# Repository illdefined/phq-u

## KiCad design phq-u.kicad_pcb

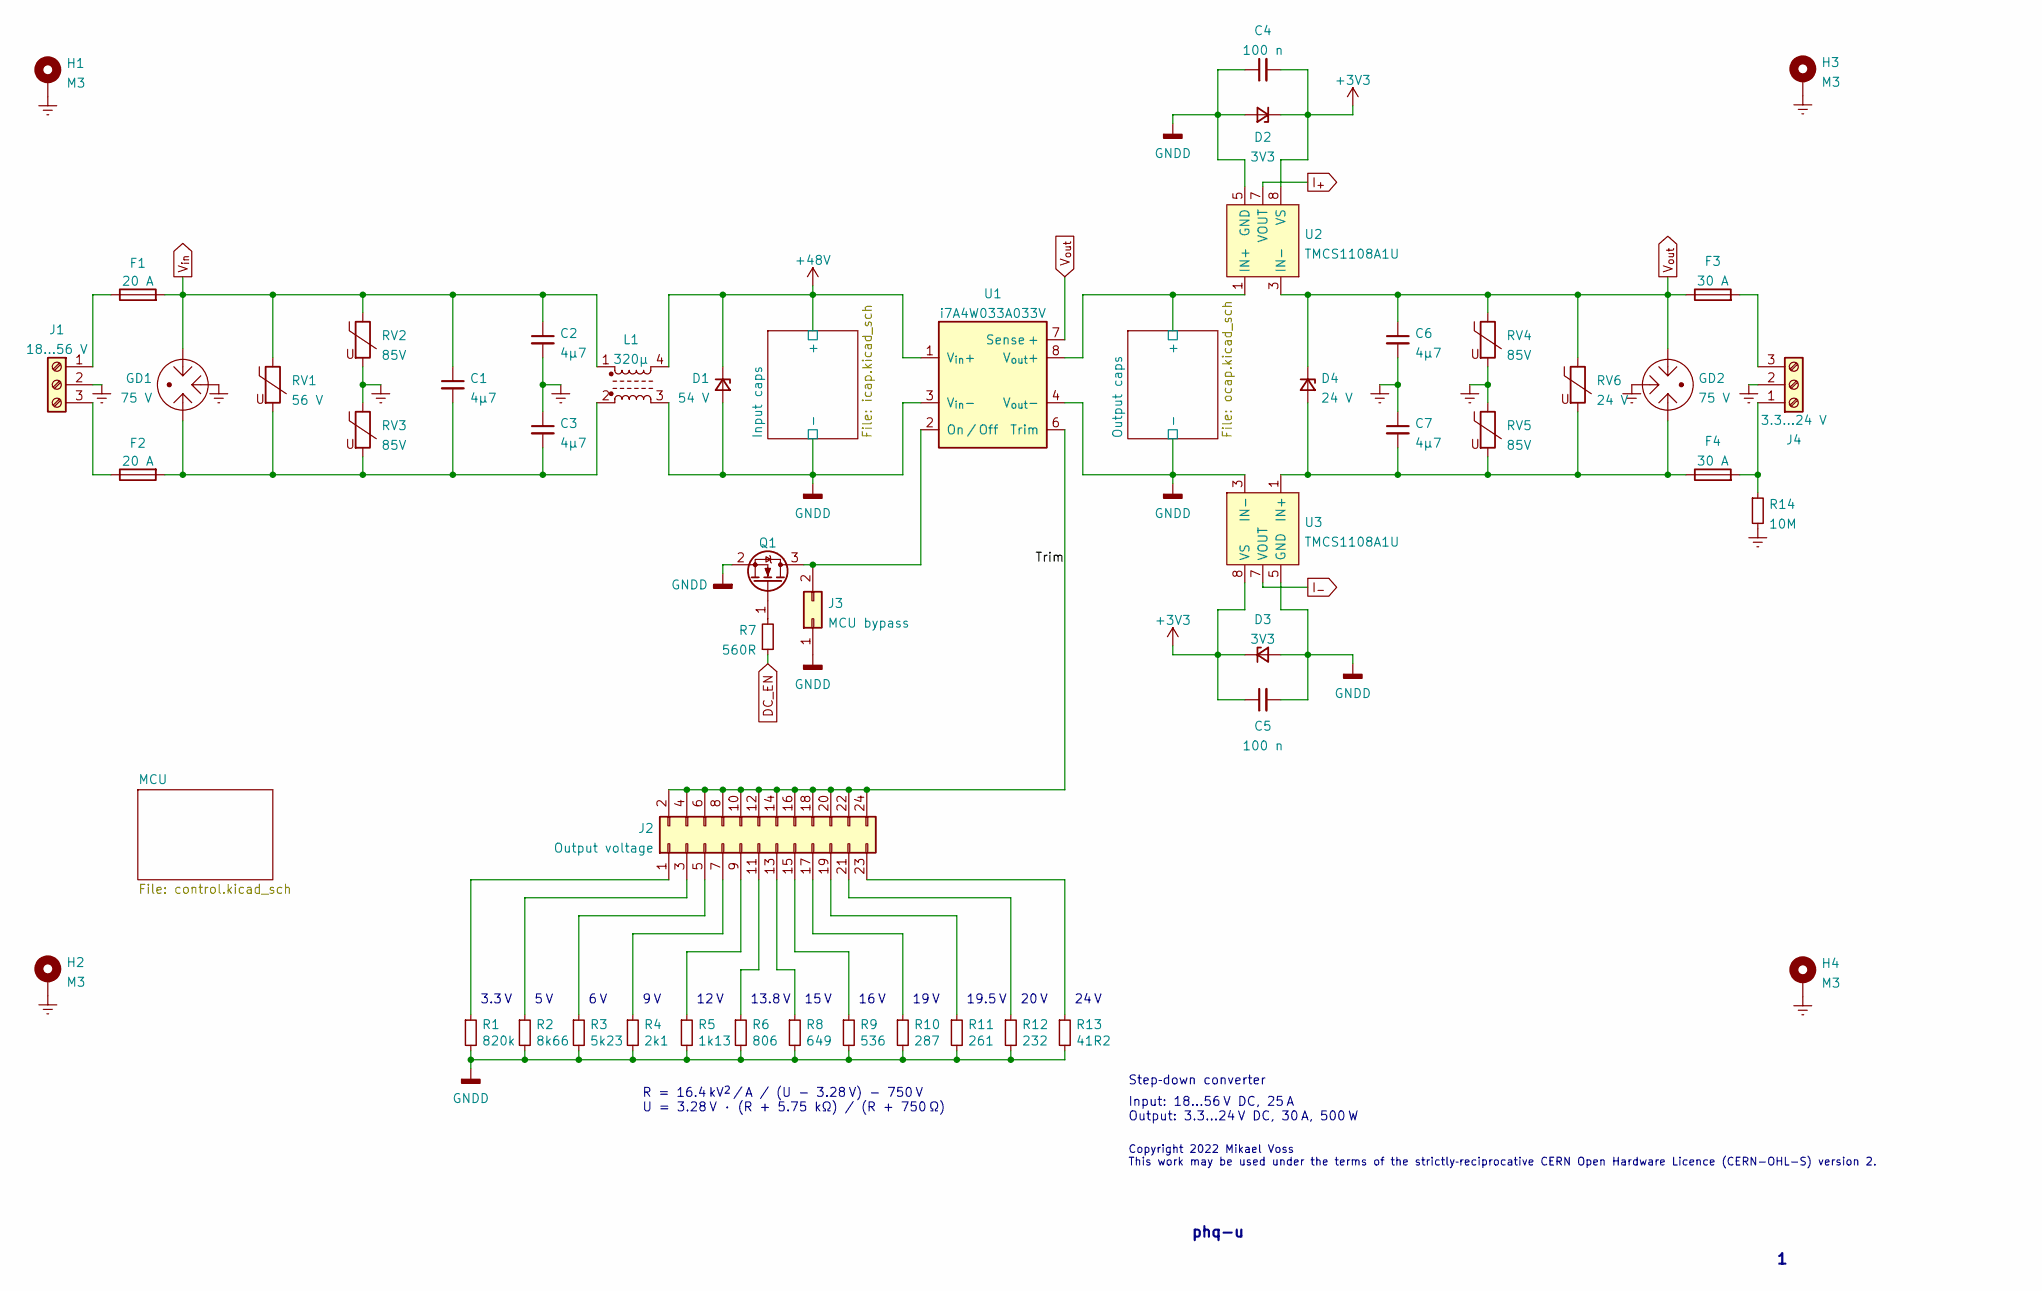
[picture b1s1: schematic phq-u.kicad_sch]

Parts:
C1, C2, C3, C6, C7: 4µ7; C_1210_3225Metric; Part Number 12101C475K4T2A
C4, C5: 100 n; C_0402_1005Metric
D1: 54 V; D_SMB; Part Number 1.5SMBJ54A-H
D2, D3: 3V3; D_0402_1005Metric; Part Number DF2S5M4CT
D4: 24 V; D_SMA; Part Number SMA6F24A
F1, F2: 20 A; Fuse_2410_20A; Part Number CB61F30A
F3, F4: 30 A; Fuse_2410_20A; Part Number CB61F30A
GD1, GD2: 75 V; 2036-NN-SM; Part Number 2036-07-SM
H1, H2, H3, H4: M3; MountingHole_3.2mm_M3_Pad_Via
J1: 18…56 V; Phoenix_1987737
J2: Output voltage; PinHeader_2x12_P2.00mm_Vertical
J3: MCU bypass; PinHeader_2x01_P2.00mm_Vertical
J4: 3.3…24 V; Phoenix_1987737
L1: 320µ; CMX1211Z321B-10
Q1: NX138AKR; SOT-23; Part Number NX138AKR
R1: 820k; R_0603_1608Metric
R2: 8k66; R_0603_1608Metric
R3: 5k23; R_0603_1608Metric
R4: 2k1; R_0603_1608Metric
R5: 1k13; R_0603_1608Metric
R6: 806; R_0603_1608Metric
R7: 560R; R_0402_1005Metric
R8: 649; R_0603_1608Metric
R9: 536; R_0603_1608Metric
R10: 287; R_0603_1608Metric
R11: 261; R_0603_1608Metric
R12: 232; R_0603_1608Metric
R13: 41R2; R_0603_1608Metric
R14: 10M; R_0603_1608Metric
RV1: 56 V; C_2220_5650Metric; Part Number B72540E0400K062
RV2, RV3, RV4, RV5: 85V; C_1206_3216Metric; Part Number ZV60K1206121NIR1
RV6: 24 V; C_1210_3225Metric; Part Number B72530T6170K062
U1: i7A4W033A033V; i7A4W-0C1; Part Number i7A4W033A033V-0C1
U2, U3: TMCS1108A1U; SOIC-8_3.9x4.9mm_P1.27mm

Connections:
+3V3: C4.2, C5.1, D2.1 (K), D3.1 (K), U2.8 (VS), U3.8 (VS); also elsewhere on the board
+48V: D1.1 (K), L1.4, U1.1 (V_{in}+); also elsewhere on the board
/Output caps/+: U1.8 (V_{out}+), U2.1 (IN+), U2.2 (IN+); also elsewhere on the board
/Trim: J2.2, J2.4, J2.6, J2.8, J2.10, J2.12, J2.14, J2.16, J2.18, J2.20, J2.22, J2.24, U1.6 (Trim)
DC_EN: R7.1; also elsewhere on the board
Earth: C2.2, C3.1, C6.2, C7.1, GD1.2, GD2.2, H1.1, H2.1, H3.1, H4.1, J1.2, J4.2, R14.2, RV2.2, RV3.1, RV4.2, RV5.1
GND: C4.1, C5.2, D1.2 (A), D2.2 (A), D3.2 (A), J3.1, L1.3, Q1.2 (S), R1.2, R2.2, R3.2, R4.2, R5.2, R6.2, R8.2, R9.2, R10.2, R11.2, R12.2, R13.2, U1.3 (V_{in}-), U1.4 (V_{out}-), U2.5 (GND), U2.6 (NC), U3.3 (IN-), U3.4 (IN-), U3.5 (GND), U3.6 (NC); also elsewhere on the board
I_{+}: U2.7 (VOUT); also elsewhere on the board
I_{-}: U3.7 (VOUT); also elsewhere on the board
unnamed: C1.2, C3.2, F2.2, GD1.3, L1.2, RV1.2, RV3.2
unnamed: C7.2, D4.2 (A), F4.1, GD2.1, RV5.2, RV6.2, U3.1 (IN+), U3.2 (IN+)
unnamed: F1.1, J1.1
unnamed: F2.1, J1.3
unnamed: F3.2, J4.3
unnamed: F4.2, J4.1, R14.1
unnamed: J2.1, R1.1
unnamed: J2.3, R2.1
unnamed: J2.5, R3.1
unnamed: J2.7, R4.1
unnamed: J2.9, R5.1
unnamed: J2.11, R6.1
unnamed: J2.13, R8.1
unnamed: J2.15, R9.1
unnamed: J2.17, R10.1
unnamed: J2.19, R11.1
unnamed: J2.21, R12.1
unnamed: J2.23, R13.1
unnamed: J3.2, Q1.3 (D), U1.2 (On / Off)
unnamed: Q1.1 (G), R7.2
V_{in}: C1.1, C2.1, F1.2, GD1.1, L1.1, RV1.1, RV2.1; also elsewhere on the board
V_{out}: C6.1, D4.1 (K), F3.1, GD2.3, RV4.1, RV6.1, U1.7 (Sense +), U2.3 (IN-), U2.4 (IN-); also elsewhere on the board

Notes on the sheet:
12 V
16 V
phq-u
R = 16.4 kV^{2} / A / (U - 3.28 V) - 750 V U = 3.28 V · (R + 5.75 kΩ) / (R + 750 Ω)
15 V
24 V
13.8 V
9 V
Copyright 2022 Mikael Voss This work may be used under the terms of the strictly‐reciprocative CERN Open Hardware Licence (CERN-OHL-S) version 2.
Input: 18…56 V DC, 25 A Output: 3.3…24 V DC, 30 A, 500 W
19.5 V
5 V
19 V
Step‐down converter
6 V
20 V
3.3 V

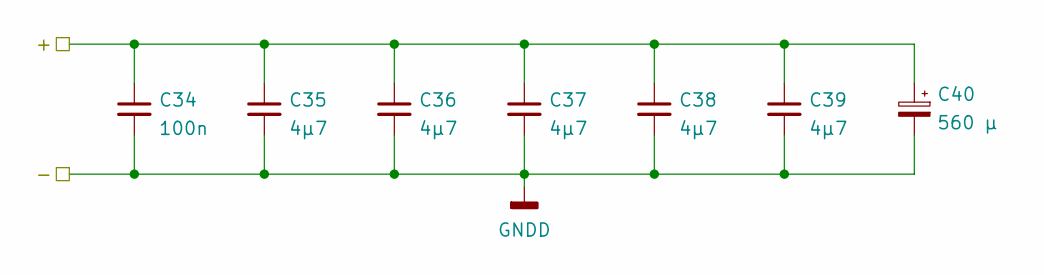
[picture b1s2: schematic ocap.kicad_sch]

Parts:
C34: 100n; C_0402_1005Metric; Part Number GRM155R71H104KE14D
C35, C36, C37, C38, C39: 4µ7; C_1206_3216Metric; Part Number 12065C475KAT2A
C40: 560 µ; CP_Radial_D10.0mm_P5.00mm; Part Number UHV1V561MPD

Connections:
/Output caps/+: C34.1, C35.1, C36.1, C37.1, C38.1, C39.1, C40.1; also elsewhere on the board
GND: C34.2, C35.2, C36.2, C37.2, C38.2, C39.2, C40.2; also elsewhere on the board

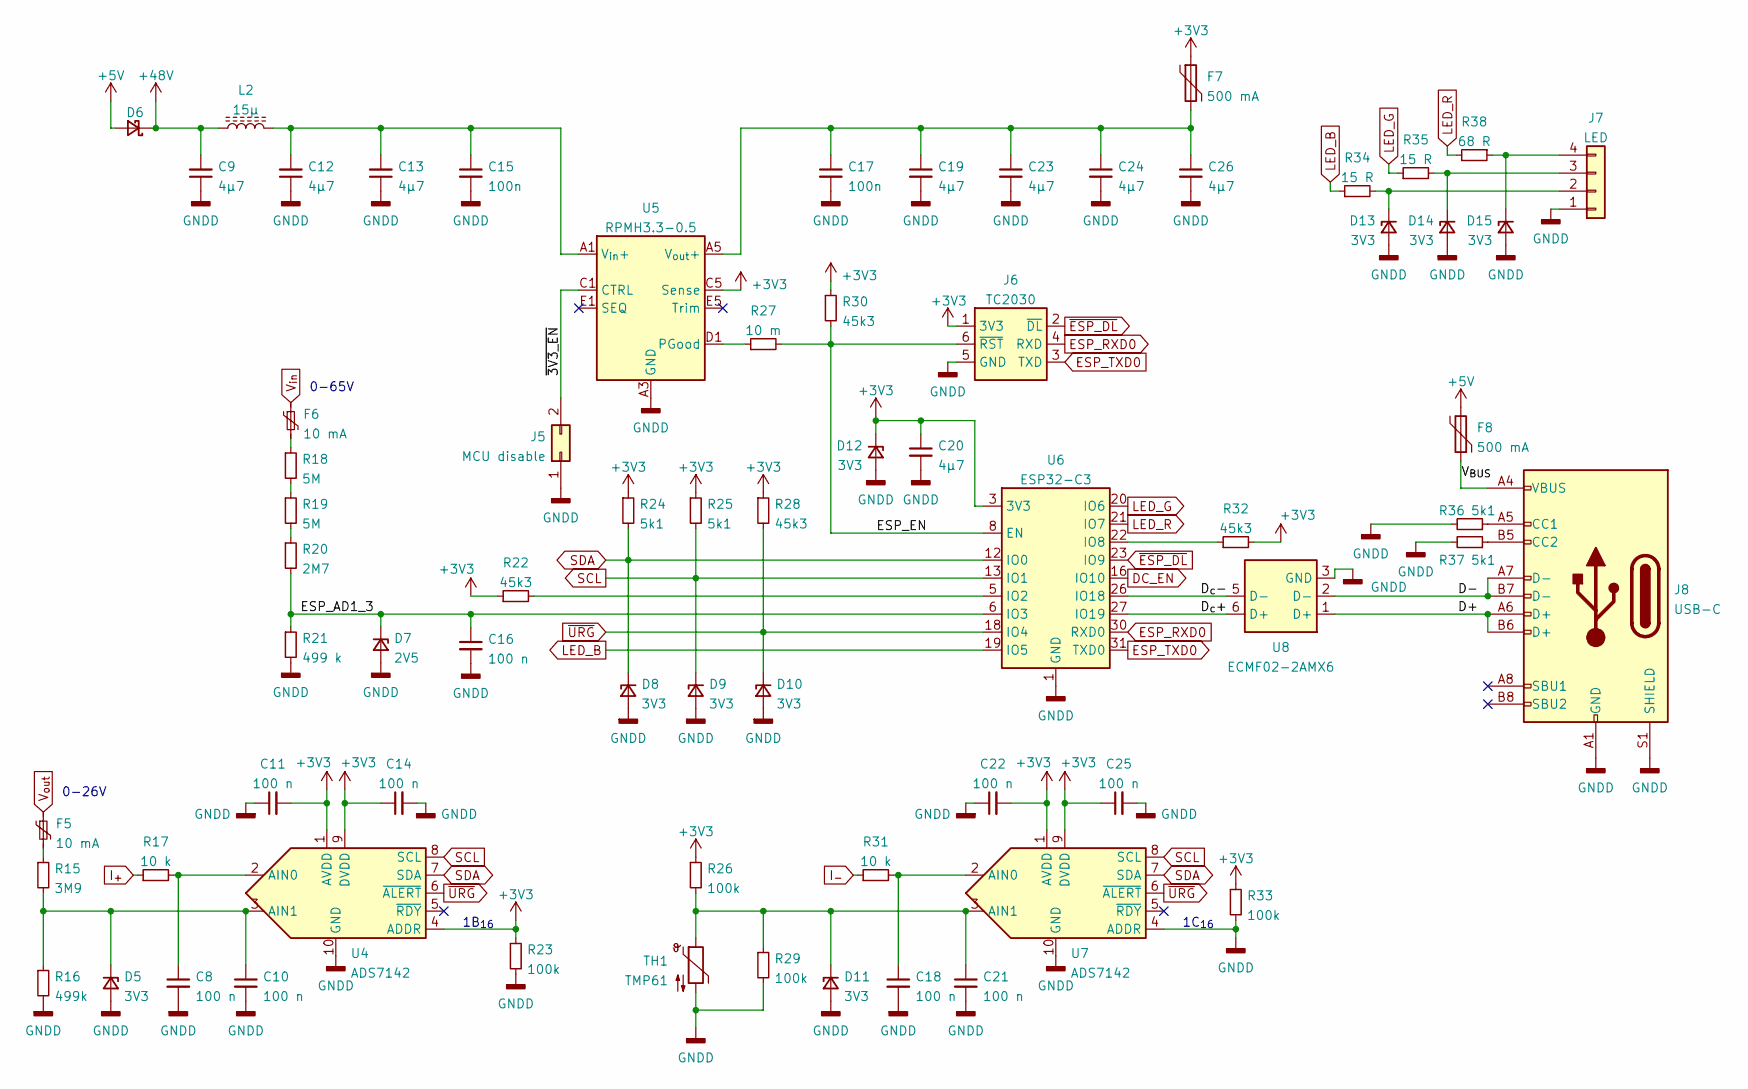
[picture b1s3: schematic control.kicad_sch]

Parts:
C8, C10, C11, C14, C18, C21, C22, C25: 100 n; C_0402_1005Metric; Part Number JMK105B7104KV-F
C9, C12, C13: 4µ7; C_1206_3216Metric; Part Number GRJ31CZ72A475KE01L
C15: 100n; C_0603_1608Metric; Part Number HMK107B7104KA
C16: 100 n; C_0402_1005Metric
C17: 100n; C_0402_1005Metric; Part Number GRM155R71E104KE14J
C19, C20, C23, C24, C26: 4µ7; C_0805_2012Metric; Part Number GRM21BR71A475KE51L
D5, D8, D9, D10, D11, D12, D13, D14, D15: 3V3; D_0402_1005Metric; Part Number DF2S5M4CT
D6: Schottky diode; D_SMF; Part Number SS1FN6
D7: 2V5; D_0402_1005Metric; Part Number UCLAMP2501T.TCT
F5, F6: 10 mA; Fuse_0603_1608Metric; Part Number 0ZCM0001FF2G
F7, F8: 500 mA; Fuse_0603_1608Metric; Part Number MF-FSML050/8-2
J5: MCU disable; PinHeader_2x01_P2.00mm_Vertical
J6: TC2030
J7: LED; PinHeader_1x04_P2.00mm_Vertical
J8: USB-C; USB4120
L2: 15µ; WE-LQS_4018; Part Number 74438356150
R15: 3M9; R_1206_3216Metric
R16: 499k; R_0805_2012Metric
R17, R31: 10 k; R_0402_1005Metric
R18, R19: 5M; R_1206_3216Metric
R20: 2M7; R_1206_3216Metric
R21: 499 k; R_0805_2012Metric
R22, R28, R30, R32: 45k3; R_0402_1005Metric
R23, R26, R29, R33: 100k; R_0402_1005Metric
R24, R25, R36, R37: 5k1; R_0402_1005Metric
R27: 10 m; R_0805_2012Metric
R34, R35: 15 R; R_0402_1005Metric
R38: 68 R; R_0402_1005Metric
TH1: TMP61; R_0402_1005Metric
U4, U7: ADS7142; Texas_R-PUQFN-N10
U5: RPMH3.3-0.5; Converter_DCDC_RECOM_RPMx.x-x.0
U6: ESP32-C3; ESP32-C3-MINI-1U
U8: ECMF02-2AMX6; ST_UQFN-6L_1.5x1.7mm_Pitch0.5mm

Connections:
+3V3: C11.2, C14.1, C20.1, C22.2, C25.1, D12.1 (K), F7.1, J6.1 (3V3), R22.1, R23.1, R24.1, R25.1, R26.1, R28.1, R30.1, R32.2, R33.1, U4.1 (AVDD), U4.4 (ADDR), U4.9 (DVDD), U5.C5 (Sense), U6.3 (3V3), U7.1 (AVDD), U7.9 (DVDD); also elsewhere on the board
+5V: D6.2 (A), F8.2
+48V: C9.2, D6.1 (K), L2.1; also elsewhere on the board
/MCU/D+: J8.A6 (D+), J8.B6 (D+), U8.1 (D+)
/MCU/D-: J8.A7 (D-), J8.B7 (D-), U8.2 (D-)
/MCU/D_{c}+: U6.27 (IO19), U8.6 (D+)
/MCU/D_{c}-: U6.26 (IO18), U8.5 (D-)
/MCU/ESP_AD1_3: C16.1, D7.1 (K), R20.2, R21.1, U6.6 (IO3)
/MCU/ESP_EN: J6.6 (~RST), R27.2, R30.2, U6.8 (EN)
/MCU/V_{BUS}: F8.1, J8.A4 (VBUS), J8.A9 (VBUS), J8.B4 (VBUS), J8.B9 (VBUS)
/MCU/~3V3_EN: J5.2, U5.C1 (CTRL)
DC_EN: U6.16 (IO10); also elsewhere on the board
ESP_RXD0: J6.4 (RXD), U6.30 (RXD0)
ESP_TXD0: J6.3 (TXD), U6.31 (TXD0)
GND: C8.2, C9.1, C10.2, C11.1, C12.1, C13.1, C14.2, C15.2, C16.2, C17.2, C18.2, C19.2, C20.2, C21.2, C22.1, C23.2, C24.2, C25.2, C26.2, D5.2 (A), D7.2 (A), D8.2 (A), D9.2 (A), D10.2 (A), D11.2 (A), D12.2 (A), D13.2 (A), D14.2 (A), D15.2 (A), J5.1, J6.5 (GND), J7.1, J8.A1 (GND), J8.A12 (GND), J8.B1 (GND), J8.B12 (GND), J8.S1 (SHIELD), J8.S2 (SHIELD), J8.S3 (SHIELD), J8.S4 (SHIELD), R16.2, R21.2, R23.2, R29.2, R33.2, R36.2, R37.2, TH1.2, U4.10 (GND), U5.A3 (GND), U5.A4 (GND), U5.B1 (GND), U5.B2 (GND), U5.B3 (GND), U5.B4 (GND), U5.C2 (GND), U5.C3 (GND), U5.C4 (GND), U5.D2 (GND), U5.D3 (GND), U5.D4 (GND), U5.D5 (GND), U5.E3 (GND), U5.E4 (GND), U6.1 (GND), U6.2 (GND), U6.11 (GND), U6.14 (GND), U6.36 (GND), U6.37 (GND), U6.38 (GND), U6.39 (GND), U6.40 (GND), U6.41 (GND), U6.42 (GND), U6.43 (GND), U6.44 (GND), U6.45 (GND), U6.46 (GND), U6.47 (GND), U6.48 (GND), U6.49_1 (GND), U6.49_2 (GND), U6.49_3 (GND), U6.49_4 (GND), U6.49_5 (GND), U6.49_6 (GND), U6.49_7 (GND), U6.49_8 (GND), U6.49_9 (GND), U6.50 (GND), U6.51 (GND), U6.52 (GND), U6.53 (GND), U7.4 (ADDR), U7.10 (GND), U8.3 (GND), U8.4 (NC); also elsewhere on the board
I_{+}: R17.1; also elsewhere on the board
I_{-}: R31.1; also elsewhere on the board
LED_B: R34.1, U6.19 (IO5)
LED_G: R35.1, U6.20 (IO6)
LED_R: R38.2, U6.21 (IO7)
unnamed: C8.1, R17.2, U4.2 (AIN0)
unnamed: C10.1, D5.1 (K), R15.2, R16.1, U4.3 (AIN1)
unnamed: C12.2, C13.2, C15.1, L2.2, U5.A1 (V_{in}+), U5.A2 (V_{in}+)
unnamed: C17.1, C19.1, C23.1, C24.1, C26.1, F7.2, U5.A5 (V_{out}+), U5.B5 (V_{out}+)
unnamed: C18.1, R31.2, U7.2 (AIN0)
unnamed: C21.1, D11.1 (K), R26.2, R29.1, TH1.1, U7.3 (AIN1)
unnamed: D13.1 (K), J7.2, R34.2
unnamed: D14.1 (K), J7.3, R35.2
unnamed: D15.1 (K), J7.4, R38.1
unnamed: F5.2, R15.1
unnamed: F6.2, R18.1
unnamed: J8.A5 (CC1), R36.1
unnamed: J8.B5 (CC2), R37.1
unnamed: R18.2, R19.1
unnamed: R19.2, R20.1
unnamed: R22.2, U6.5 (IO2)
unnamed: R27.1, U5.D1 (PGood)
unnamed: R32.1, U6.22 (IO8)
SCL: D9.1 (K), R25.2, U4.8 (SCL), U6.13 (IO1), U7.8 (SCL)
SDA: D8.1 (K), R24.2, U4.7 (SDA), U6.12 (IO0), U7.7 (SDA)
V_{in}: F6.1; also elsewhere on the board
V_{out}: F5.1; also elsewhere on the board
~ESP_DL: J6.2 (~DL), U6.23 (IO9)
~URG: D10.1 (K), R28.2, U4.6 (~ALERT), U6.18 (IO4), U7.6 (~ALERT)

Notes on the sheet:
1C_{16}
0-26V
0-65V
1B_{16}

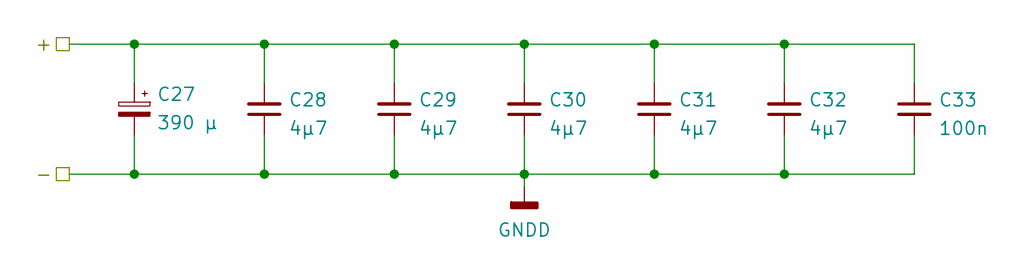
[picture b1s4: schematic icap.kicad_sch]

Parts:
C27: 390 µ; CP_Radial_D12.5mm_P5.00mm; Part Number UHW1J391MHD6
C28, C29, C30, C31, C32: 4µ7; C_1206_3216Metric; Part Number GRJ31CZ72A475KE01L
C33: 100n; C_0603_1608Metric; Part Number HMK107B7104KA

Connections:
+48V: C27.1, C28.2, C29.2, C30.2, C31.2, C32.2, C33.1; also elsewhere on the board
GND: C27.2, C28.1, C29.1, C30.1, C31.1, C32.1, C33.2; also elsewhere on the board

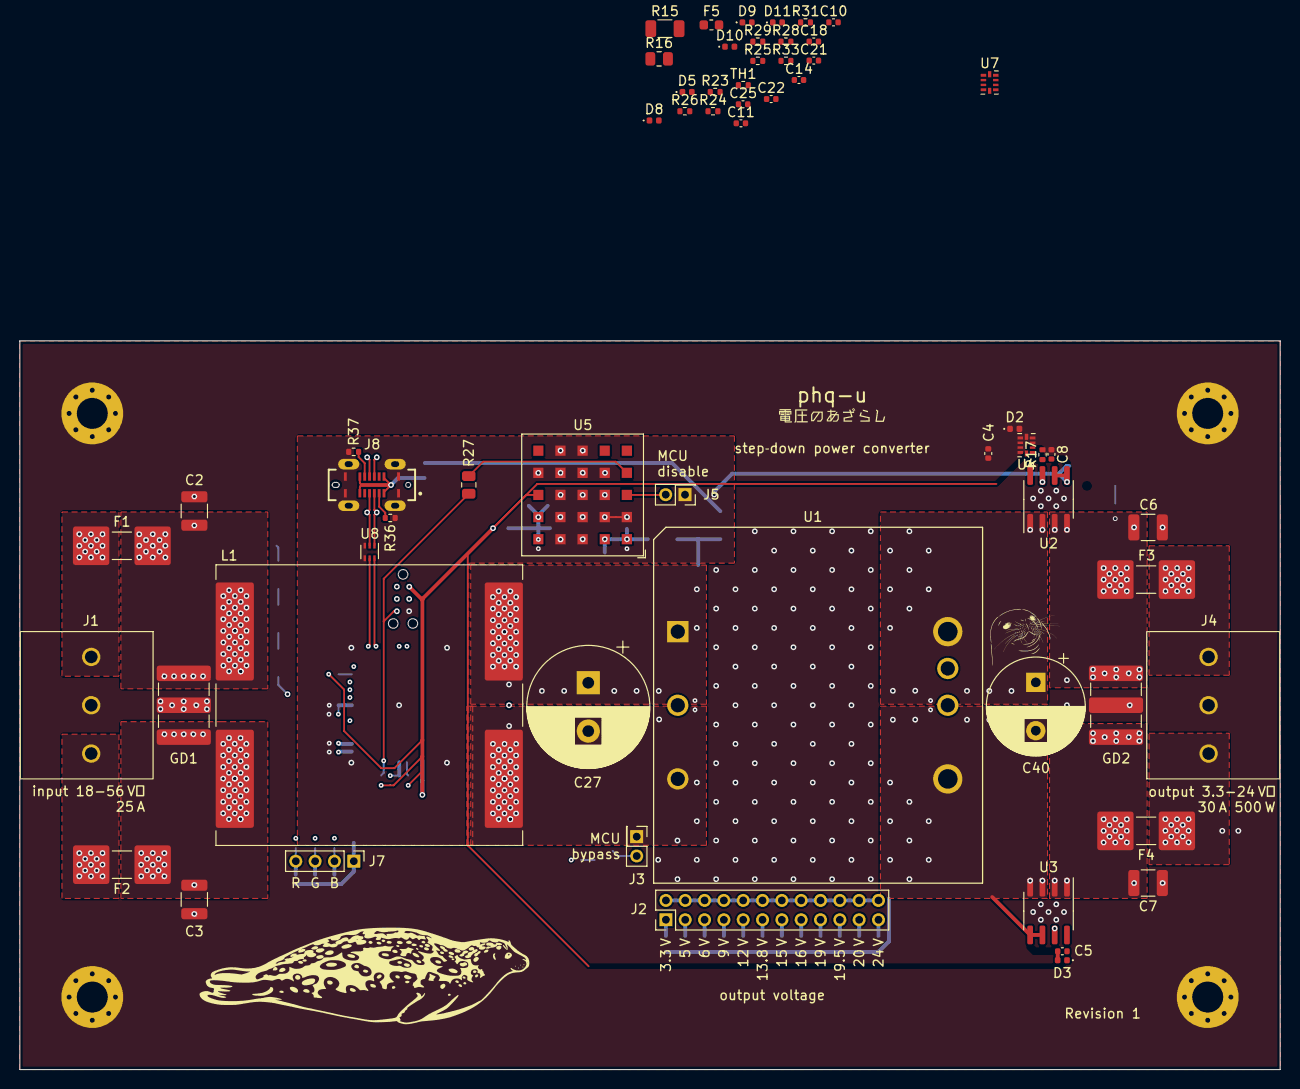
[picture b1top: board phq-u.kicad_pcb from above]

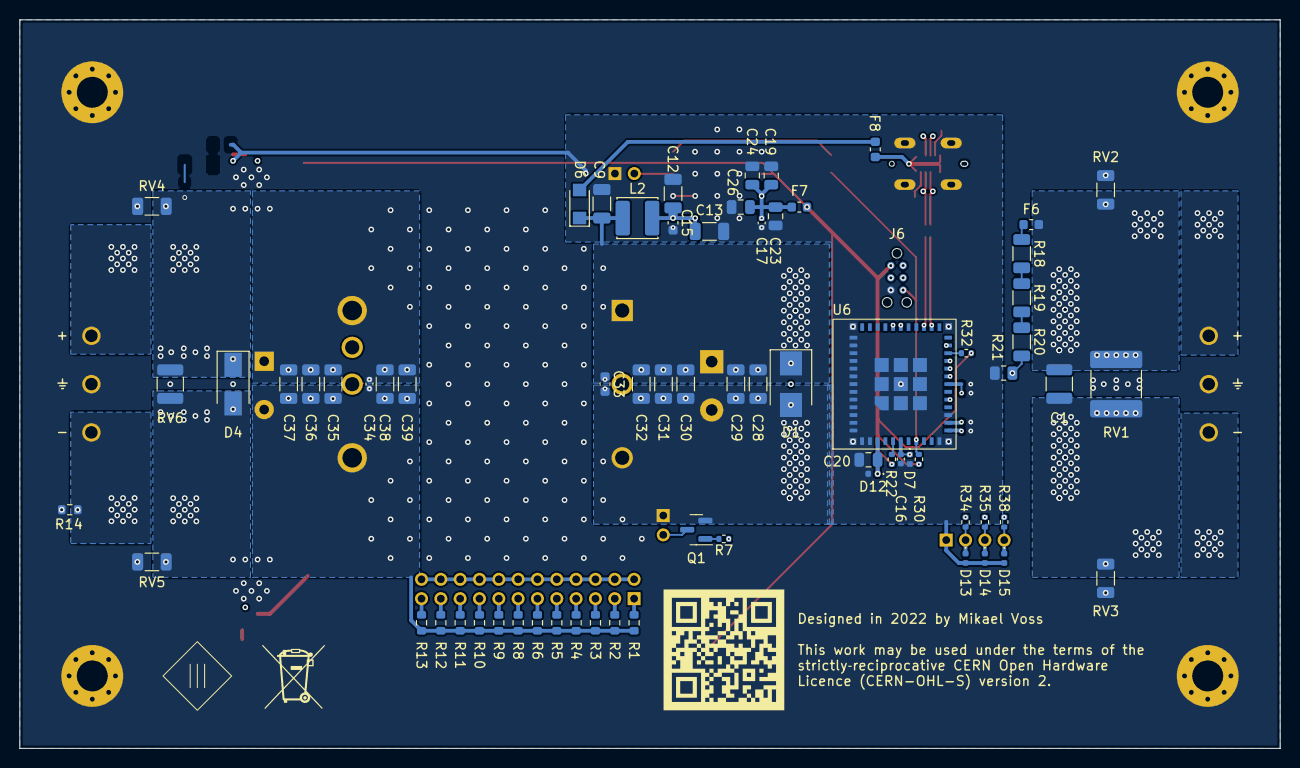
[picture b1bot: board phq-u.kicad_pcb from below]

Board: 4 copper layers, 130.4 x 75.4 mm, 133 parts (69 on the bottom side), 67 nets.

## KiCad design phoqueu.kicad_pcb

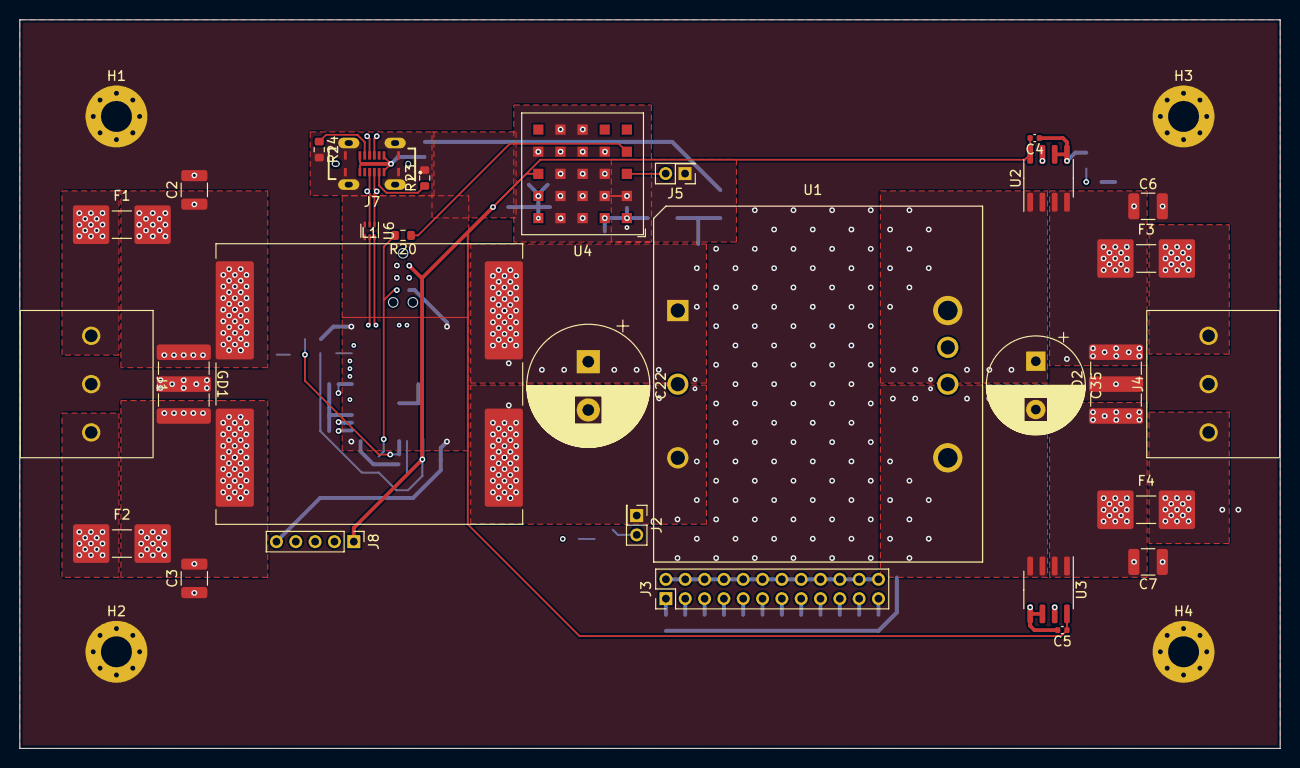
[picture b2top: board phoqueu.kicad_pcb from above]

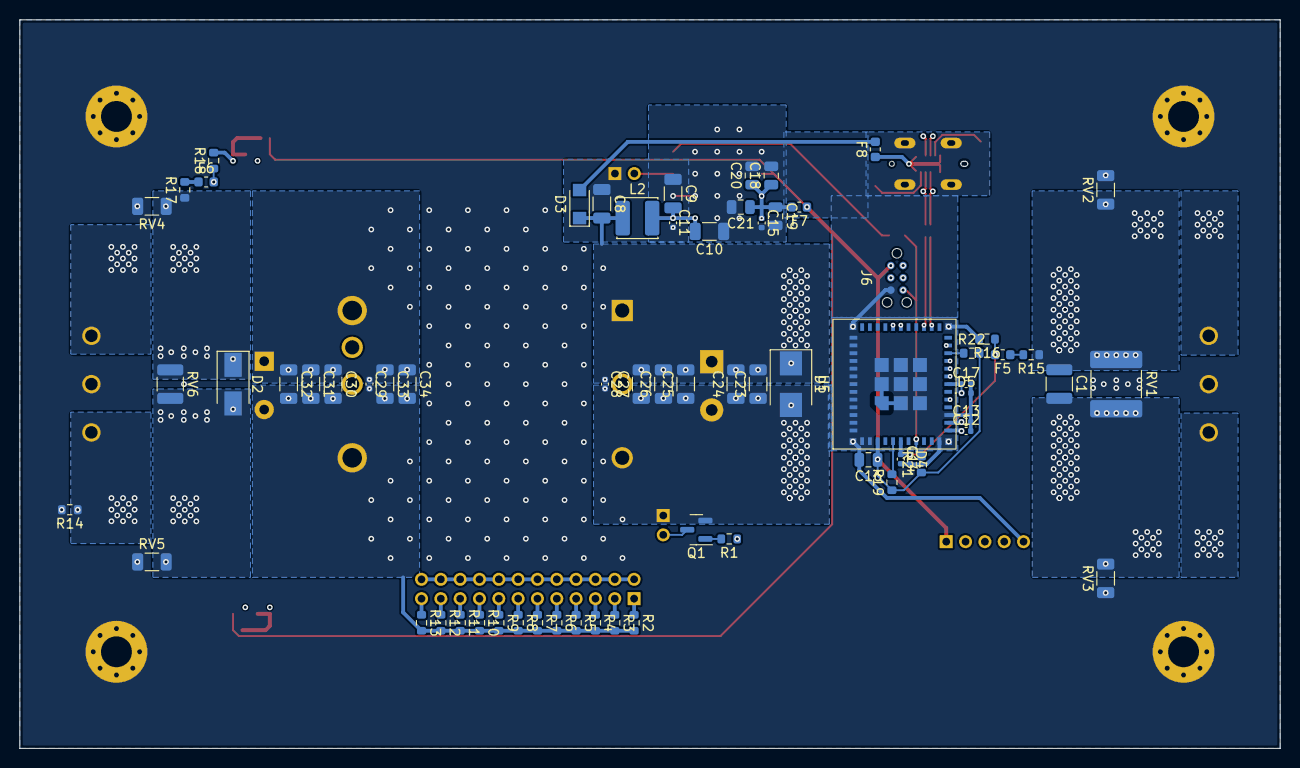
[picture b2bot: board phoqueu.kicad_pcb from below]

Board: 4 copper layers, 130.4 x 75.4 mm, 101 parts (67 on the bottom side), 56 nets.

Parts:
C1, C2, C3, C6, C7: 4µ7; C_1210_3225Metric
C4, C5, C12, C13, C14, C17: 100 n; C_0402_1005Metric
C8, C9, C10, C23, C24, C25, C26, C27, C30, C31, C32, C33, C34: 4µ7; C_1206_3216Metric
C11, C15, C28, C29: 100n; C_0402_1005Metric
C16, C18, C19, C20, C21: 4µ7; C_0805_2012Metric
C22: 390 µ; CP_Radial_D12.5mm_P5.00mm
C35: 560 µ; CP_Radial_D10.0mm_P5.00mm
D1: 54 V; D_SMB
D2: 24 V; D_SMA
D3: Schottky diode; D_SMF
D4, D5: 2V5; D_0402_1005Metric
F1, F2, F3, F4: 30 A; Fuse_2410_20A
F5, F6: 10 mA; Fuse_0603_1608Metric
F7, F8: 500 mA; Fuse_0603_1608Metric
GD1, GD2: 75 V; 2036-NN-SM
H1, H2, H3, H4: M3; MountingHole_3.2mm_M3_Pad_Via
J1: 18…56 V; Phoenix_1987737
J2: MCU bypass; PinHeader_2x01_P2.00mm_Vertical
J3: Voltage select; PinHeader_2x12_P2.00mm_Vertical
J4: 3.3…24 V; Phoenix_1987737
J5: MCU disable; PinHeader_2x01_P2.00mm_Vertical
J6: TC2030
J7: USB-C; USB4120
J8: I/O; PinHeader_1x05_P2.00mm_Vertical
L1: 320µ; CMX1211Z321B-10
L2: 15µ; WE-LQS_4018
Q1: NX138AK; SOT-23
R1: 560R; R_0603_1608Metric
R2: 820k; R_0603_1608Metric
R3: 8k76; R_0603_1608Metric
R4: 5k23; R_0603_1608Metric
R5: 2k1; R_0603_1608Metric
R6: 1k13; R_0603_1608Metric
R7: 806; R_0603_1608Metric
R8: 649; R_0603_1608Metric
R9: 536; R_0603_1608Metric
R10: 294; R_0603_1608Metric
R11: 261; R_0603_1608Metric
R12: 232; R_0603_1608Metric
R13: 41R2; R_0603_1608Metric
R14: 10M; R_0603_1608Metric
R15: 25M; R_0603_1608Metric
R16: 1M; R_0603_1608Metric
R17: 4M7; R_0603_1608Metric
R18: 500k; R_0603_1608Metric
R19, R21, R22: 45k3; R_0603_1608Metric
R20: 0; R_0603_1608Metric
R23, R24: 5k1; R_0603_1608Metric
RV1: 56 V; C_2220_5650Metric
RV2, RV3, RV4, RV5: 85V; C_1206_3216Metric
RV6: 24 V; C_1210_3225Metric
U1: i7A4W033A033V; i7A4W-0C1
U2, U3: TMCS1108A1U; SOIC-8_3.9x4.9mm_P1.27mm
U4: RPMH3.3-0.5; Converter_DCDC_RECOM_RPMx.x-x.0
U5: ESP32-C3; ESP32-C3-MINI-1U
U6: ECMF02-2AMX6; ST_UQFN-6L_1.5x1.7mm_Pitch0.5mm

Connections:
+3V3: C4.2, C5.1, C16.1, F7.1, J6.1 (3V3), J8.1, R19.1, R21.1, R22.2, U2.8 (VS), U3.8 (VS), U4.C5 (Sense), U5.3 (3V3)
+5V: D3.2 (A), F8.2
+48V: C8.2, C22.1, C23.2, C24.2, C25.2, C26.2, C27.2, C28.1, D1.1 (K), D3.1 (K), L1.4, L2.1, U1.1 (V_{in}+)
/MCU/D+: J7.A6 (D+), J7.B6 (D+), U6.1 (D+)
/MCU/D-: J7.A7 (D-), J7.B7 (D-), U6.2 (D-)
/MCU/D_{c}+: U5.27 (IO19), U6.6 (D+)
/MCU/D_{c}-: U5.26 (IO18), U6.5 (D-)
/MCU/ESP_AD1_3: C14.1, D4.1 (K), F5.2, R16.1, U5.6 (IO3)
/MCU/ESP_AD1_4: C17.1, D5.1 (K), F6.2, R18.1, U5.18 (IO4)
/MCU/ESP_EN: J6.6 (~RST), R20.2, R21.2, U5.8 (EN)
/MCU/V_{BUS}: F8.1, J7.A4 (VBUS), J7.A9 (VBUS), J7.B4 (VBUS), J7.B9 (VBUS)
/MCU/~3V3_EN: J5.2, U4.C1 (CTRL)
/Output caps/in+: C29.1, C30.1, C31.1, C32.1, C33.1, C34.1, C35.1, U1.8 (V_{out}+), U2.1 (IN+), U2.2 (IN+)
/Trim: J3.2, J3.4, J3.6, J3.8, J3.10, J3.12, J3.14, J3.16, J3.18, J3.20, J3.22, J3.24, U1.6 (Trim)
/V_{inr}+: F1.1, J1.1
/V_{inr}-: F2.1, J1.3
/V_{out}+: F3.2, J4.3
/V_{out}-: F4.2, J4.1, R14.1
ESP_AD1_0: C12.1, U3.7 (VOUT), U5.12 (IO0)
ESP_AD1_1: C13.1, U2.7 (VOUT), U5.13 (IO1)
ESP_IO5: J8.2, U5.19 (IO5)
ESP_IO6: J8.3, U5.20 (IO6)
ESP_IO7: J8.4, U5.21 (IO7)
ESP_IO9: J6.2 (~DL), U5.23 (IO9)
ESP_IO10: R1.1, U5.16 (IO10)
ESP_RXD0: J6.4 (RXD), U5.30 (RXD0)
ESP_TXD0: J6.3 (TXD), U5.31 (TXD0)
Earth: C2.2, C3.1, C6.2, C7.1, GD1.2, GD2.2, H1.1, H2.1, H3.1, H4.1, J1.2, J4.2, R14.2, RV2.2, RV3.1, RV4.2, RV5.1
GND: C4.1, C5.2, C8.1, C9.1, C10.1, C11.2, C12.2, C13.2, C14.2, C15.2, C16.2, C17.2, C18.2, C19.2, C20.2, C21.2, C22.2, C23.1, C24.1, C25.1, C26.1, C27.1, C28.2, C29.2, C30.2, C31.2, C32.2, C33.2, C34.2, C35.2, D1.2 (A), D4.2 (A), D5.2 (A), J2.1, J5.1, J6.5 (GND), J7.A1 (GND), J7.A12 (GND), J7.B1 (GND), J7.B12 (GND), J7.S1 (SHIELD), J7.S2, J7.S3, J7.S4, J8.5, L1.3, Q1.2 (S), R2.2, R3.2, R4.2, R5.2, R6.2, R7.2, R8.2, R9.2, R10.2, R11.2, R12.2, R13.2, R16.2, R18.2, R23.2, R24.2, U1.3 (V_{in}-), U1.4 (V_{out}-), U2.5 (GND), U2.6 (NC), U3.3 (IN-), U3.4 (IN-), U3.5 (GND), U3.6 (NC), U4.A3 (GND), U4.A4 (GND), U4.B1 (GND), U4.B2 (GND), U4.B3 (GND), U4.B4 (GND), U4.C2 (GND), U4.C3 (GND), U4.C4 (GND), U4.D2 (GND), U4.D3 (GND), U4.D4 (GND), U4.D5 (GND), U4.E3 (GND), U4.E4 (GND), U5.1 (GND), U5.2 (GND), U5.11 (GND), U5.14 (GND), U5.36 (GND), U5.37 (GND), U5.38 (GND), U5.39 (GND), U5.40 (GND), U5.41 (GND), U5.42 (GND), U5.43 (GND), U5.44 (GND), U5.45 (GND), U5.46 (GND), U5.47 (GND), U5.48 (GND), U5.49_1 (GND), U5.49_2 (GND), U5.49_3 (GND), U5.49_4 (GND), U5.49_5 (GND), U5.49_6 (GND), U5.49_7 (GND), U5.49_8 (GND), U5.49_9 (GND), U5.50 (GND), U5.51 (GND), U5.52 (GND), U5.53 (GND), U6.3 (GND), U6.4 (NC)
unnamed: C1.2, C3.2, F2.2, GD1.3, L1.2, RV1.2, RV3.2
unnamed: C7.2, D2.2 (A), F4.1, GD2.1, RV5.2, RV6.2, U3.1 (IN+), U3.2 (IN+)
unnamed: C9.2, C10.2, C11.1, L2.2, U4.A1 (V_{in}+), U4.A2 (V_{in}+)
unnamed: C15.1, C18.1, C19.1, C20.1, C21.1, F7.2, U4.A5 (V_{out}+), U4.B5 (V_{out}+)
unnamed: F5.1, R15.2
unnamed: F6.1, R17.2
unnamed: J2.2, Q1.3 (D), U1.2 (On / Off)
unnamed: J3.3, R3.1
unnamed: J3.17, R10.1
unnamed: J3.19, R11.1
unnamed: J3.21, R12.1
unnamed: J3.23, R13.1
unnamed: J7.A5 (CC1), R23.1
unnamed: J7.B5 (CC2), R24.1
unnamed: Q1.1 (G), R1.2
unnamed: J3.1, R2.1
unnamed: J3.5, R4.1
unnamed: J3.7, R5.1
unnamed: J3.9, R6.1
unnamed: J3.11, R7.1
unnamed: J3.13, R8.1
unnamed: J3.15, R9.1
unnamed: R19.2, U5.5 (IO2)
unnamed: R20.1, U4.D1 (PGood)
unnamed: R22.1, U5.22 (IO8)
V_{in}: C1.1, C2.1, F1.2, GD1.1, L1.1, R15.1, RV1.1, RV2.1
V_{out}: C6.1, D2.1 (K), F3.1, GD2.3, R17.1, RV4.1, RV6.1, U1.7 (Sense +), U2.3 (IN-), U2.4 (IN-)

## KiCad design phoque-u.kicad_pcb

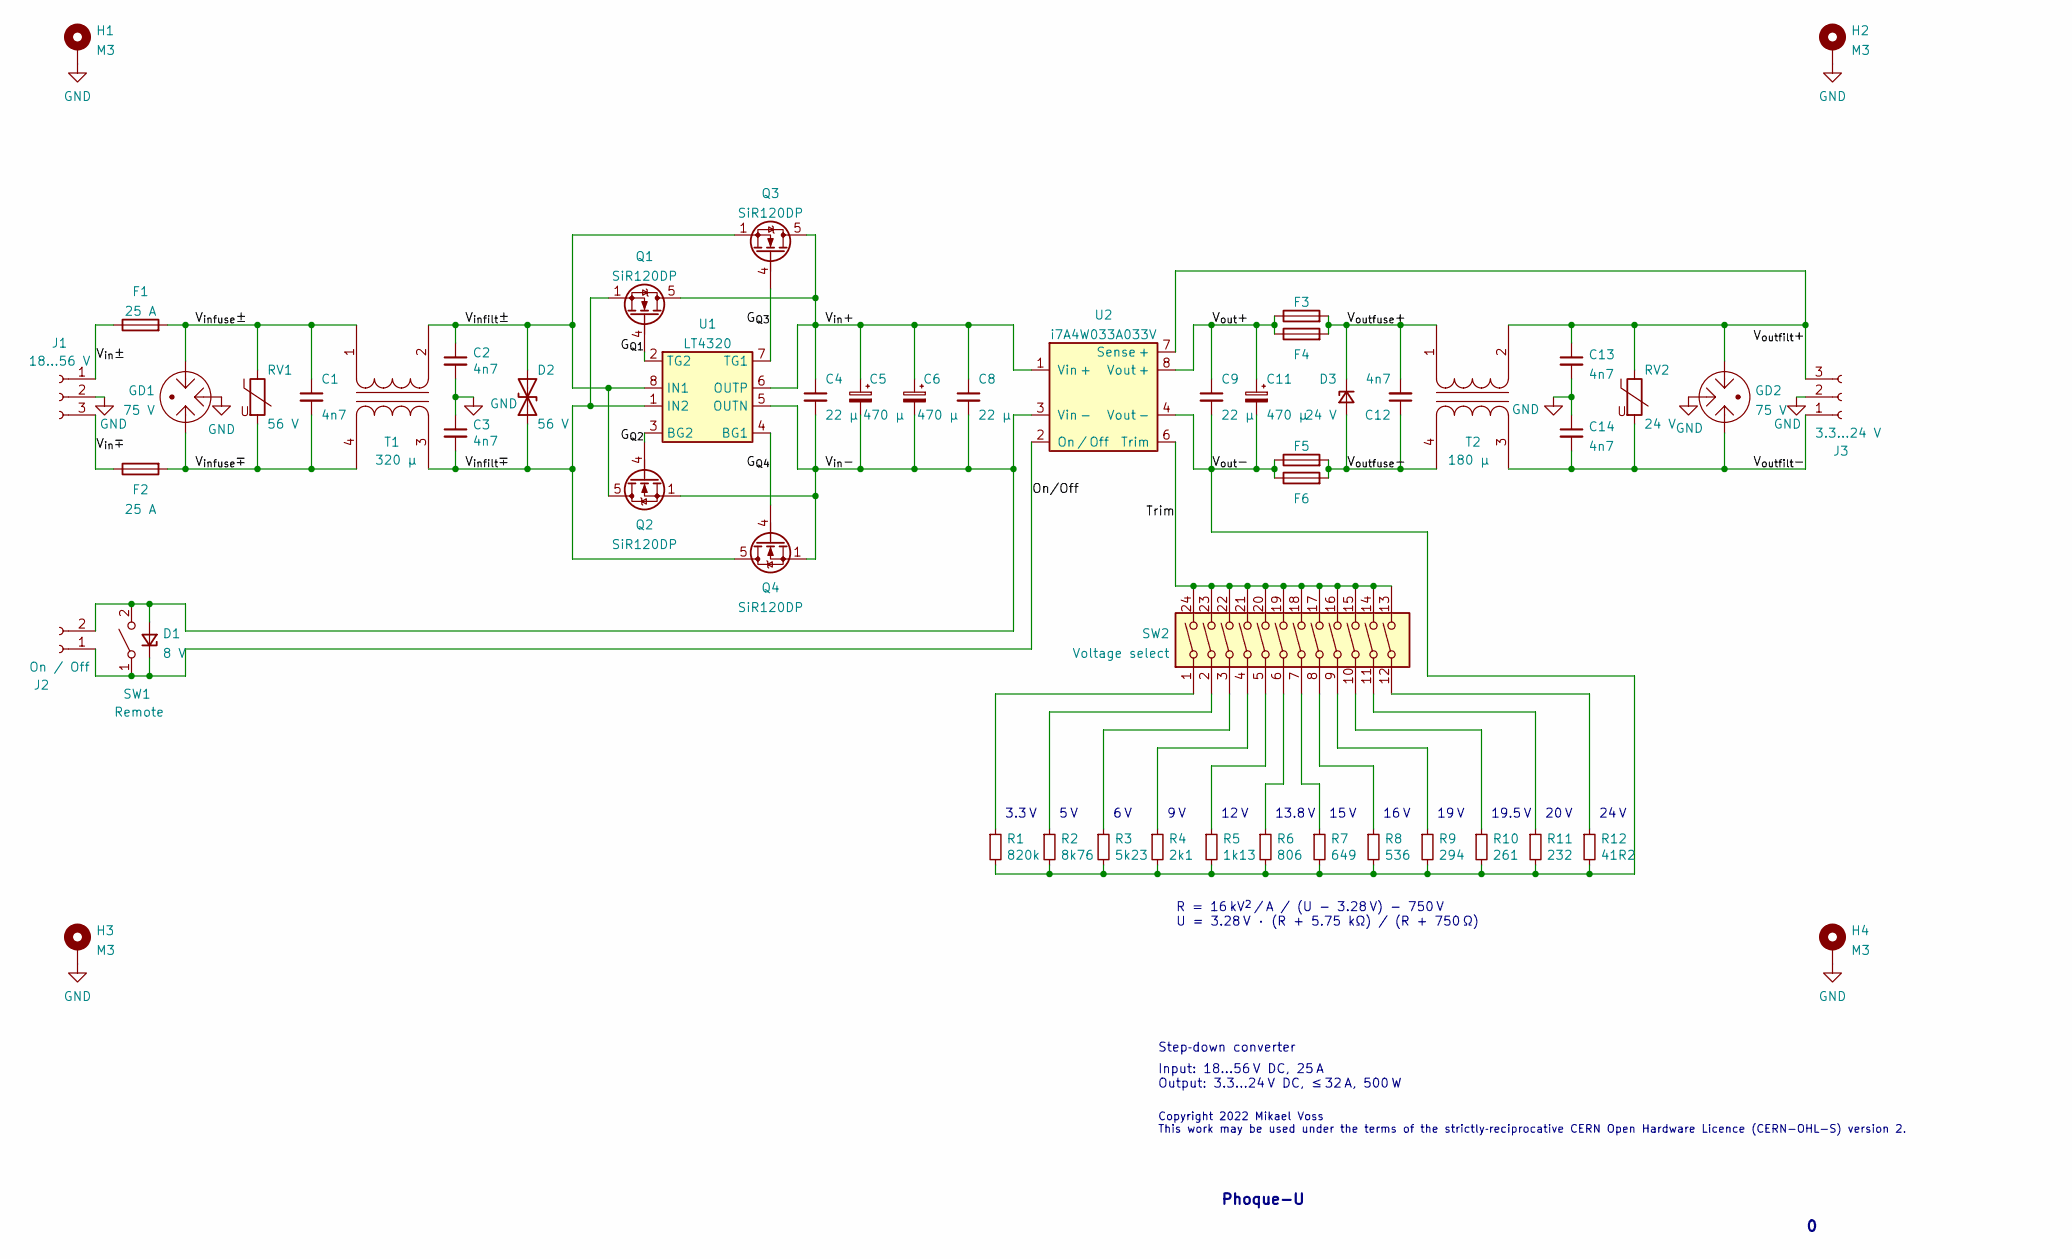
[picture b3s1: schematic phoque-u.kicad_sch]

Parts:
C1, C2, C3, C12, C13, C14: 4n7; C_Disc_D13mm_W6.0mm_P10.00mm; Part Number CD45-E2GA472M-NKA
C4, C8, C9: 22 µ; KRM55WR71J226MH01; Part Number KRM55WR71J226MH01K
C5, C6, C11: 470 µ; CP_Radial_D16.0mm_P7.50mm; Part Number URZ1J471MHD
D1: 8 V; D_SMF; Part Number SMF8.0A
D2: 56 V; D_BZW50-56B_P12.70mm_Horizontal; Part Number BZW50-56B
D3: 24 V; D_SMC; Part Number SMC30J24A
F1: 25 A; 3557; Part Number 3557
F2: 25 A; 3557
F3, F5: ≤ 32 A; 3557; Part Number 3557
F4, F6: ≤ 32 A; 8040; Part Number 8040.0003
GD1, GD2: 75 V; 2036-NN-SM; Part Number 2036-07-SM
H1, H2, H3, H4: M3; MountingHole_3.2mm_M3_Pad_Via
J1: 18…56 V; 2606-1103; Part Number 2606-1103
J2: On / Off; 2604-1102; Part Number 2604-1102
J3: 3.3…24 V; 2606-1103; Part Number 2606-1103
Q1, Q3, Q4: SiR120DP; Vishay_PowerPAK_1212-8_Single
Q2: SiR120DP; Vishay_PowerPAK_1212-8_Single; Part Number SiR120DP
R1: 820k; R_0805_2012Metric
R2: 8k76; R_0805_2012Metric
R3: 5k23; R_0805_2012Metric
R4: 2k1; R_0805_2012Metric
R5: 1k13; R_0805_2012Metric
R6: 806; R_0805_2012Metric
R7: 649; R_0805_2012Metric
R8: 536; R_0805_2012Metric
R9: 294; R_0805_2012Metric
R10: 261; R_0805_2012Metric
R11: 232; R_0805_2012Metric
R12: 41R2; R_0805_2012Metric
RV1: 56 V; R_0805_2012Metric; Part Number B72540E0400K062
RV2: 24 V; R_0805_2012Metric; Part Number B72530T6170K062
SW1: Remote; 418127160901; Part Number 418127160901
SW2: Voltage select; 418127160912; Part Number 418127160901
T1: 320 µ; CMX1211Z321B-10; Part Number CMX1211Z321B-10
T2: 180 µ; CMX1211Z181B-10; Part Number CMX1211Z181B-10
U1: LT4320; DFN-8-1EP_3x3mm_P0.5mm_EP1.65x2.38mm
U2: i7A4W033A033V; i7A4W033A033V-0C1; Part Number i7A4W033A033V-0C1

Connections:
/G_{Q1}: Q1.4 (G), U1.2 (TG2)
/G_{Q2}: Q2.4 (G), U1.3 (BG2)
/G_{Q3}: Q3.4 (G), U1.7 (TG1)
/G_{Q4}: Q4.4 (G), U1.4 (BG1)
/On/Off: D1.1 (K), J2.1, SW1.1 (A), U2.2 (On / Off)
/Trim: SW2.13, SW2.14, SW2.15, SW2.16, SW2.17, SW2.18, SW2.19, SW2.20, SW2.21, SW2.22, SW2.23, SW2.24, U2.6 (Trim)
/V_{infilt}±: C2.1, D2.2 (A2), Q2.5 (D), Q3.1 (S), Q3.2 (S), Q3.3 (S), T1.2 (AB), U1.8 (IN1)
/V_{infilt}∓: C3.2, D2.1 (A1), Q1.1 (S), Q1.2 (S), Q1.3 (S), Q4.5 (D), T1.3 (SA), U1.1 (IN2)
/V_{infuse}±: C1.1, F1.2, GD1.1, RV1.1, T1.1 (AA)
/V_{infuse}∓: C1.2, F2.2, GD1.3, RV1.2, T1.4 (SB)
/V_{in}+: C4.1, C5.1, C6.1, C8.1, Q1.5 (D), Q3.5 (D), U1.6 (OUTP), U2.1 (Vin +)
/V_{in}-: C4.2, C5.2, C6.2, C8.2, D1.2 (A), J2.2, Q2.1 (S), Q2.2 (S), Q2.3 (S), Q4.1 (S), Q4.2 (S), Q4.3 (S), SW1.2 (B), U1.5 (OUTN), U1.9 (OUTN), U2.3 (Vin -)
/V_{in}±: F1.1, J1.1
/V_{in}∓: F2.1, J1.3
/V_{outfilt}+: C13.1, GD2.3, J3.3, RV2.1, T2.2 (AB), U2.7 (Sense +)
/V_{outfilt}-: C14.2, GD2.1, J3.1, RV2.2, T2.3 (SA)
/V_{outfuse}+: C12.2, D3.1 (K), F3.2, F4.2, T2.1 (AA)
/V_{outfuse}-: C12.1, D3.2 (A), F5.2, F6.2, T2.4 (SB)
/V_{out}+: C9.1, C11.1, F3.1, F4.1, U2.8 (Vout +)
/V_{out}-: C9.2, C11.2, F5.1, F6.1, R1.2, R2.2, R3.2, R4.2, R5.2, R6.2, R7.2, R8.2, R9.2, R10.2, R11.2, R12.2, U2.4 (Vout -)
GND: C2.2, C3.1, C13.2, C14.1, GD1.2, GD2.2, H1.1, H2.1, H3.1, H4.1, J1.2, J3.2
unnamed: R1.1, SW2.1
unnamed: R2.1, SW2.2
unnamed: R3.1, SW2.3
unnamed: R4.1, SW2.4
unnamed: R5.1, SW2.5
unnamed: R6.1, SW2.6
unnamed: R7.1, SW2.7
unnamed: R8.1, SW2.8
unnamed: R9.1, SW2.9
unnamed: R10.1, SW2.10
unnamed: R11.1, SW2.11
unnamed: R12.1, SW2.12

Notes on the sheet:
12 V
16 V
Phoque-U
R = 16 kV^{2} / A / (U - 3.28 V) - 750 V U = 3.28 V · (R + 5.75 kΩ) / (R + 750 Ω)
15 V
24 V
13.8 V
9 V
Copyright 2022 Mikael Voss This work may be used under the terms of the strictly‐reciprocative CERN Open Hardware Licence (CERN-OHL-S) version 2.
Input: 18…56 V DC, 25 A Output: 3.3…24 V DC, ≤ 32 A, 500 W
19.5 V
5 V
19 V
Step‐down converter
6 V
20 V
3.3 V
